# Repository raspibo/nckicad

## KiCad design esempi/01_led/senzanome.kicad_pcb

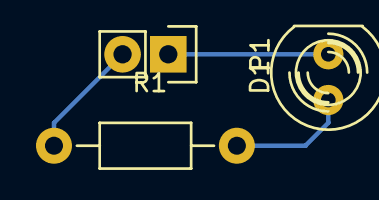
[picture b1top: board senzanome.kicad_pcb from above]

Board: 2 copper layers, 3 parts (0 on the bottom side), 3 nets.

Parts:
D1: LED; LED-5MM
P1: CONN_01X02; Pin_Header_Straight_1x02
R1: R; Resistor_Horizontal_RM10mm

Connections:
GND: D1.2, P1.1
unnamed: D1.1, R1.2
VCC: P1.2, R1.1

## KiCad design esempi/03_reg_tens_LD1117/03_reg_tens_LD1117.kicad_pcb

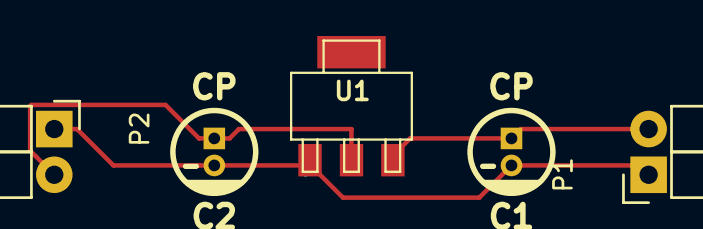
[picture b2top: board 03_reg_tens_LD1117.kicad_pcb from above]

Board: 2 copper layers, 5 parts (0 on the bottom side), 3 nets.

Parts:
C1, C2: CP; CP_4x5mm
P1, P2: CONN_01X02; Socket_Strip_Angled_1x02
U1: LD1117S33TR; sot223

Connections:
GND: C1.2, C2.2, P1.1, P2.1, U1.1
unnamed: C1.1, P1.2, U1.3
unnamed: C2.1, P2.2, U1.2

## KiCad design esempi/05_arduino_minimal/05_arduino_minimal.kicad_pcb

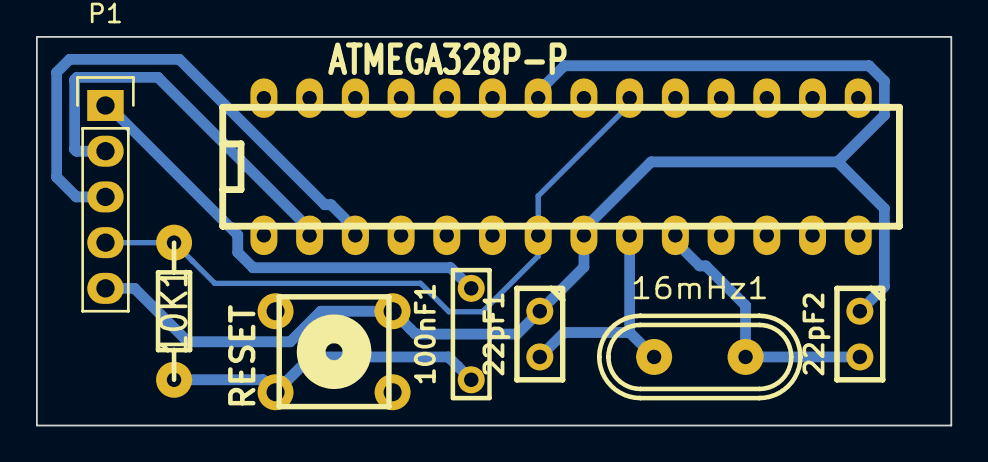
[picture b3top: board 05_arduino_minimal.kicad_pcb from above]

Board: 2 copper layers, 50.8 x 21.6 mm, 8 parts (0 on the bottom side), 8 nets.

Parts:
10K1: R; RC03
16mHz1: Crystal; crystal_hc-49u
22pF1, 22pF2: C; cnp_3mm_disc
100nF1: C; cnp_7.5mm_disc
IC1: ATMEGA328P-P; dil_28-300
P1: CONN_01X05; Pin_Header_Straight_1x05
SW1: RESET; PCB_PUSH

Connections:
GND: 22pF1.1, 22pF2.1, IC1.8, IC1.22, P1.5, SW1.2
unnamed: 16mHz1.1, 22pF1.2, IC1.9
unnamed: 16mHz1.2, 22pF2.2, IC1.10
unnamed: 100nF1.1, P1.1
unnamed: 10K1.2, 100nF1.2, SW1.1
unnamed: IC1.2, P1.2
unnamed: IC1.3, P1.3
VCC: 10K1.1, IC1.7, IC1.20, P1.4
